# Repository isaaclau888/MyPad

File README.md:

# MyPad

MyPad is a tiny, pocket-sized macro pad I designed to clear up my desk and speed up my workflow. It has 9 mechanical keys, a vertical screen, and a dial knob, all packed into a super clean layout inspired by the classic look of the original 2001 Apple iPod. Instead of having a massive grid of keys, MyPad relies on clever software. By using multiple code layers and custom shortcuts, this little 3x3 pad can handle everything from jumping through complex lines of code in VS Code to tweaking 3D models in Fusion 360, all without my hand ever leaving the controller.

## What's it for?
MyPad is a tiny, physical shortcut box for your desk that saves you from stretching your fingers across awkward keyboard shortcuts. It condenses repetitive tasks—like copy-pasting, opening a terminal, or switching layers—into single tactile clicks. Plus, the built-in screen keeps track of your settings while the dial knob gives you smooth, hands-on control over your music volume or timeline scrolling.

## How to build it?
Please print all the 3D parts. <p>

# 3D Parts Assembly
Step 1: Solder the Base Electronics <br>
Solder all base components directly onto your PCB. This includes the Seeed Studio XIAO RP2040, the SSD1306 OLED Screen, the IN4148 Diodes, and the EC11 Rotary Encoder. Ensure they sit flat against the PCB surface before soldering. <p>

Step 2: Prepare the Top Plate <br>
Take your top case part (which acts as your top switch plate). Push all of your mechanical switches into the 14.0mm x 14.0mm square cutouts from the top side until they click tightly into place. <p>

Step 3: Combine and Solder the Switches <br>
Align the metal pins of the switches (now held in the top plate) with the empty switch holes on your PCB. Press the top plate assembly firmly down onto the PCB until the bottom of the switches rest flush against the PCB. Flip the assembly over and solder the switch pins from the back of the PCB. <p>

Step 4: Mount into the Bottom Case <br>
Place your fully soldered core assembly into the bottom case. Make sure the Seeed Studio XIAO's USB-C port aligns perfectly with the cutout pocket in the case wall, then secure the top and bottom halves together using your housing screws. <p>

Step 5: Final Touches <br>
Push your keycaps onto the switch stems. Your MyPad is complete! <p>

## How to Install Firmware?

1. Copy Folder to QMK
Clone this repository, then copy or move the **`MyPad Firmware`** folder into your local QMK directory:
`qmk_firmware/keyboards/`

2. Compile the Code
Open your terminal inside your `qmk_firmware` folder and run this command: qmk compile -kb "MyPad Firmware" -km default <p>
(Make sure to keep the quotation marks around the folder name in your terminal so it reads the space correctly!) This creates a file named `mypad_firmware_default.uf2`.

3. Flash the RP2040

4. Unplug the USB-C cable from your MyPad.
  
5. Hold down the physical **BOOTSEL** button on the tiny XIAO board while plugging the cable back into your computer.

6. A folder named **RPI-RP2** will pop up on your computer like a regular USB flash drive.

7. Drag and drop the `.uf2` file right into that folder. <p>

The drive will automatically close itself, and your MyPad is ready to go!

## Why did I make it?
I decided to make this because I want a custom keyboard that works like a Stream Deck.

## How I made it?
I used Fusion 360 to make the case, VS Code and Terminal for the coding part, KiCad for the PCB board and last but not least, the parts from the BOM.

# Schematic and PCB

# BOM

|   |                                           |    |           |                 |          |        |              |              |              |                                                                                                                                                                                                                                                                                                                                                                                                                                                                                                                                                                                                                              |                      |
|---|-------------------------------------------|----|-----------|-----------------|----------|--------|--------------|--------------|--------------|------------------------------------------------------------------------------------------------------------------------------------------------------------------------------------------------------------------------------------------------------------------------------------------------------------------------------------------------------------------------------------------------------------------------------------------------------------------------------------------------------------------------------------------------------------------------------------------------------------------------------|----------------------|
|   |Description                                |Item|Usage Count|Purchase Quantity|Unit Price|Subtotal|Price(HKD) [$]|Price(RMB) [$]|Price(USD) [$]|Link                                                                                                                                                                                                                                                                                                                                                                                                                                                                                                                                                                                                                          |Additional description|
|   |Electrical Components                      |    |           |                 |          |        |              |              |              |                                                                                                                                                                                                                                                                                                                                                                                                                                                                                                                                                                                                                              |                      |
|   |PCB Board                                  |    |1          |1                |$54.86    |$54.86  |$54.86        |$47.39        |$7.00         |https://jlcpcb.com/                                                                                                                                                                                                                                                                                                                                                                                                                                                                                                                                                                                                           |                      |
|   |Seeed Studio XIAO RP2040                   |    |1          |1                |$28.94    |$28.94  |$28.94        |$25.00        |$3.69         |https://item.taobao.com/item.htm?id=658626117798&spm=a312a.7700824.w4002-26059791966.9.60d933db6lhayb&skuId=5902864067685                                                                                                                                                                                                                                                                                                                                                                                                                                                                                                     |                      |
|   |Cherry MX Switches                         |    |9          |1                |$23.15    |$23.15  |$23.15        |$20.00        |$2.95         |https://item.taobao.com/item.htm?id=615897479067&mi_id=0000G49e9UiDHmvNbZuIxEqx0hhavdGOtj9aIAB91MIe1Xs&skuId=5076329578956&spm=a21xtw.29978518.0.0&xxc=shop                                                                                                                                                                                                                                                                                                                                                                                                                                                                   |                      |
|   |SSD1306 0.91 OLED 4pin 128x32              |    |1          |1                |$14.31    |$14.31  |$14.31        |$12.36        |$1.83         |https://detail.tmall.com/item.htm?abbucket=10&id=617450807815&pisk=haVnhu_M-U1gsNB9ovmTOubTxOCvjU4bu0dpUXrGUuUYpYRK9Y7uccd-p9ZRrRqzfvnEvwGoUurEUun8JXaINu_-M7NnbFu47BRr4GfKoQlPDiCozING2kpenp1eQVosrBJrLuua74nZ8pRz4ckZu4REabrz7N0ou4REavJZbq3oaLkeTVRZP2oyYQke_N0Sb0lraulNS4iZ4blPy6zhP04-iJ8sbs9JaQPhOv0fGcRyZ5D-KmRxjMB6dxMuxvVOtng3Qr0r-u1XOXkuL-lUZifn_rwTYVqPmLxE3LJkcPaLzK6NvZ48KxEwHtPGSrEQF8AerJj7BSa_ohIPiGN_xPaDY9j5dceYW5YADwwg7-FgcC7Vli4gYREBbtf8Z8NASmnW4YIpSA3NyNbM3-ME525ASNvWzvusSmQGSK5ZLVgFM&rn=3f79f2344ea3bbee7ca7e121c52b7942&skuId=5074992704097&spm=a312a.7700824.w4011-23941273512.47.1fdd6dcbe1g9gy|                      |
|   |Rotary Encoder EC11E Switch Vertical H20mm |    |1          |1                |$3.36     |$3.36   |$3.36         |$2.90         |$0.43         |https://detail.tmall.com/item.htm?abbucket=10&id=614080038092&pisk=hNdshEfvYFghm1fqL2bDZ8fgSs5vXnSV0EIA5MjTuAb4GpTJxZ5qmEQvGn-dgtnG_ItBk3gGucA2drTkA2oraZqgFbfu65FT0wId7m46wDhySFjczpXtdKPL3N73HSKABMeduMFTHiKA9MQlv5QY6sIKRZjdDsBADXhdoNFTXsCxRJQVyiEAMsILJZb1ksCvDe3CoMQOMsKvJ2_cyKRKqPLrkzj1SqPPCgLKKSenuNCPVFCzTWzc5EXbYsVtNMpwHC5p6D3O9UveXw1SGr_BFeCO5ncus1LJJKKFHSy9gsot5E8JyQeolXnBoe9kJ-ckGdKCaCYzSjDS2CYfthrZJYiJOB-CLfqqeBpDbExYKXRKeBLBUKemgCokLLR6sRh9n-czJyKHBFw2qOQh8muIR88cBwbC52gQn-XO-w5IR2wyo&rn=da8786ba5e99918c28a8c938c6b7e189&spm=a312a.7700824.w4011-23941273512.42.49ed6dcbJybH2l&skuId=4495430251556|                      |
|   |1u Keycaps                                 |    |9          |1                |$11.58    |$11.58  |$11.58        |$10.00        |$1.48         |https://item.taobao.com/item.htm?id=739962388435&spm=a312a.7700824.w4002-15015765193.11.7d6ea607QcT1D0&skuId=5107854577164                                                                                                                                                                                                                                                                                                                                                                                                                                                                                                    |                      |
|   |IN4148 switching diodes, through-hole DO-35|    |9          |1                |$5.33     |$5.33   |$5.33         |$4.60         |$0.68         |https://detail.tmall.com/item.htm?abbucket=10&id=41209807837&pisk=ha7Se2Td3yXyKUYU0SY1krYoZe8pJ9JeL6ppNKv-87XERpBRNHHyzHPBOK1947XFLi9CHt9RzuvERv6ATb-d8p7BreYdSGHN3Y4v9CzEJpd-qzUa2Rya7yixSKyCT0FfAtnvsKd-yBK8GmdeTedpweFXHBOMp4BpJS1vnBo-yLpJkKdBwbLpp3KAMQRJpY3pexFXtKdJw9LLGEpD9epdpeQ8GZeiw8nmTpdTTV-WBsEmJxNewFv1wC0jlDA5tHiXC4U6HgSdzEQ8H7LAsiWJGFaIOIs1MUd5KP0ky1CAvHSm80Qe8yyFqs5NKxaQXZfl1TjxZ5q7T1YRb6mzV74FzEQR0jr1R-JAaU-_o2qNrwWPn9Umpl_dy6SB0XiV2Rppu6CIgVSnxPlxMt4QECBp2IA4LSNjb6xJiIO7GSinx3dDgENbGc5h.&rn=cc2dcf6003a317450cddac3927fc9ef0&spm=a312a.7700824.w4011-25323366171.258.76c21ebbyisjSf            |                      |
|   |                                           |    |           |                 |Total     |        |$141.53       |$122.25       |$18.06        |                                                                                                                                                                                                                                                                                                                                                                                                                                                                                                                                                                                                                              |                      |

# Fallout Zine

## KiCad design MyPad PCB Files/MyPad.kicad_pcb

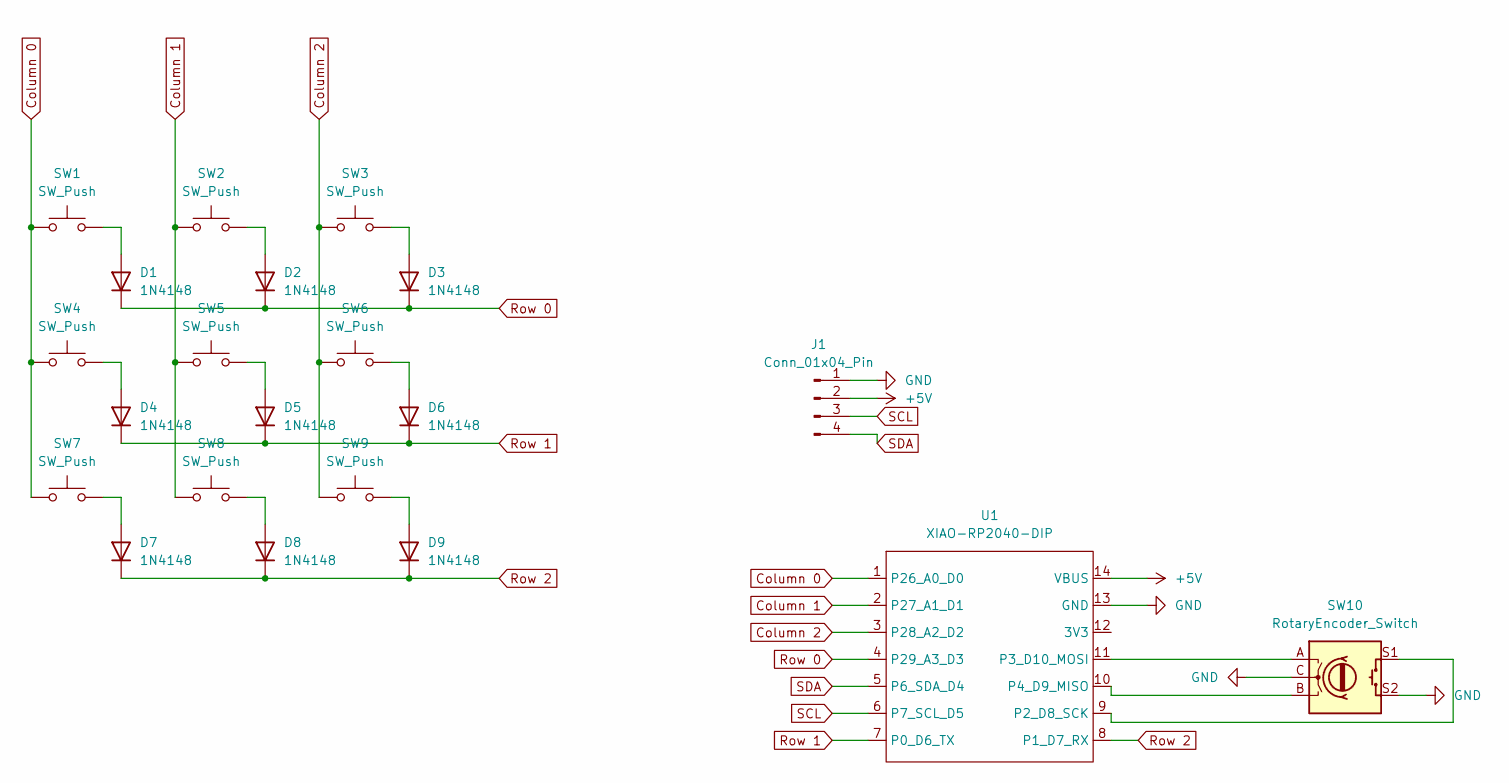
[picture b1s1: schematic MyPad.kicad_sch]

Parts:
D1, D2, D3, D4, D5, D6, D7, D8, D9: 1N4148; D_DO-35_SOD27_P7.62mm_Horizontal
J1: Conn_01x04_Pin; SSD1306-0.91-OLED-4pin-128x32
SW1, SW2, SW3, SW4, SW5, SW6, SW7, SW8, SW9: SW_Push; SW_Cherry_MX_1.00u_PCB
SW10: RotaryEncoder_Switch; RotaryEncoder_Alps_EC11E-Switch_Vertical_H20mm
U1: XIAO-RP2040-DIP

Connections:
+5V: J1.2, U1.14 (VBUS)
Column 0: SW1.1, SW4.1, SW7.1, U1.1 (P26_A0_D0)
Column 1: SW2.1, SW5.1, SW8.1, U1.2 (P27_A1_D1)
Column 2: SW3.1, SW6.1, SW9.1, U1.3 (P28_A2_D2)
GND: J1.1, SW10.C, SW10.S2, U1.13 (GND)
unnamed: D1.2 (A), SW1.2
unnamed: D2.2 (A), SW2.2
unnamed: D3.2 (A), SW3.2
unnamed: D4.2 (A), SW4.2
unnamed: D5.2 (A), SW5.2
unnamed: D6.2 (A), SW6.2
unnamed: D7.2 (A), SW7.2
unnamed: D8.2 (A), SW8.2
unnamed: D9.2 (A), SW9.2
unnamed: SW10.S1, U1.9 (P2_D8_SCK)
unnamed: SW10.A, U1.11 (P3_D10_MOSI)
unnamed: SW10.B, U1.10 (P4_D9_MISO)
Row 0: D1.1 (K), D2.1 (K), D3.1 (K), U1.4 (P29_A3_D3)
Row 1: D4.1 (K), D5.1 (K), D6.1 (K), U1.7 (P0_D6_TX)
Row 2: D7.1 (K), D8.1 (K), D9.1 (K), U1.8 (P1_D7_RX)
SCL: J1.3, U1.6 (P7_SCL_D5)
SDA: J1.4, U1.5 (P6_SDA_D4)

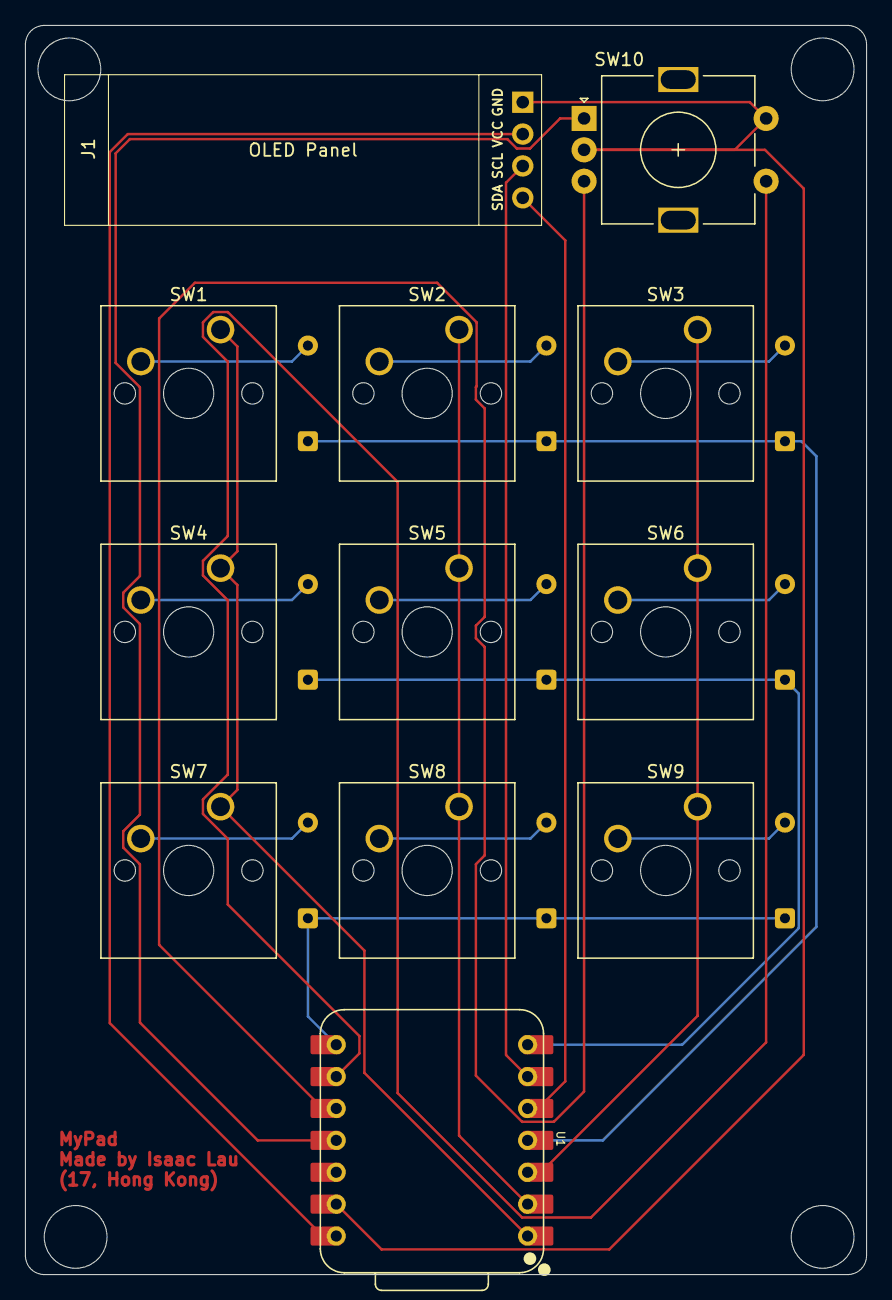
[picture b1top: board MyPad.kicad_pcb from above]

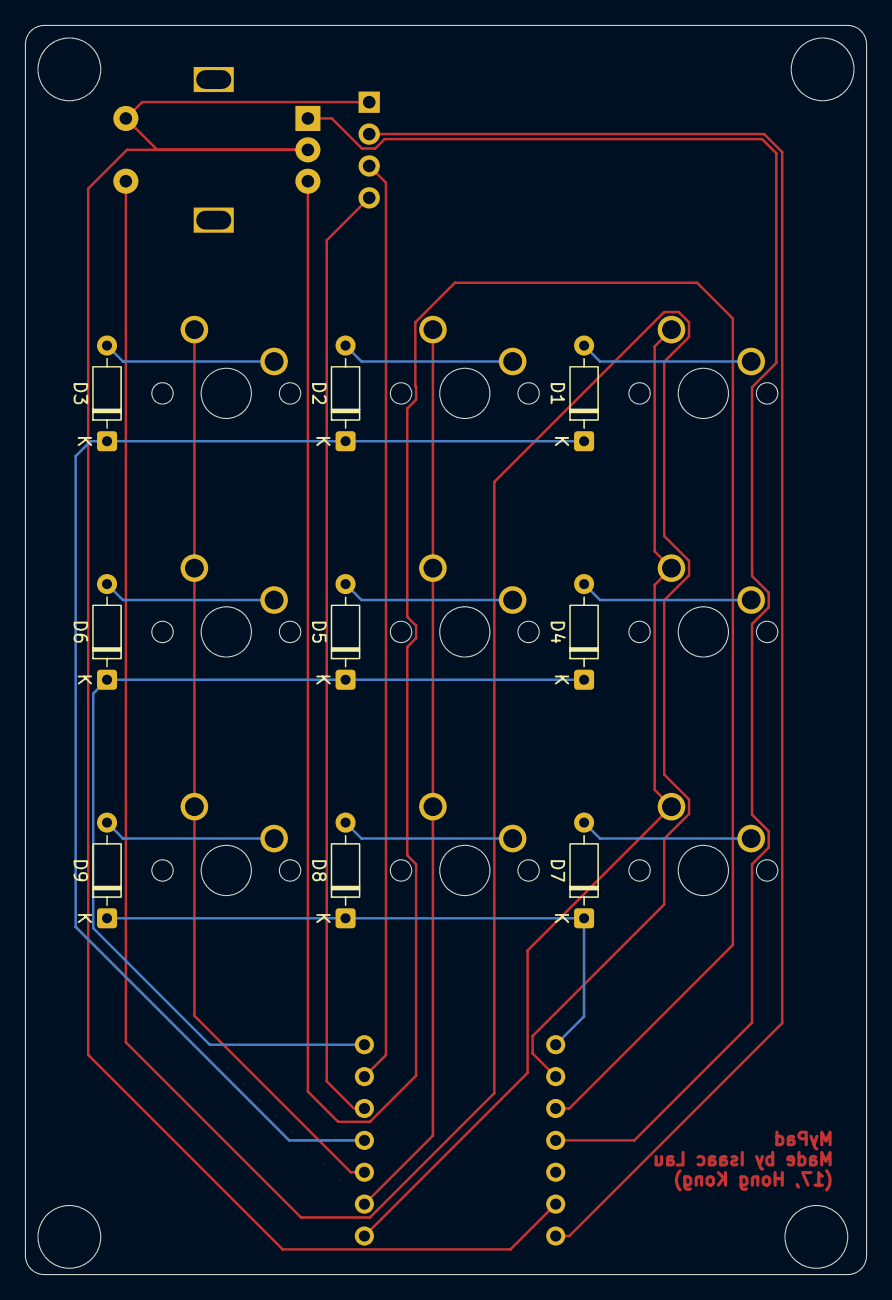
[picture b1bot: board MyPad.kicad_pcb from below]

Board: 2 copper layers, 67.0 x 99.5 mm, 21 parts (9 on the bottom side), 22 nets.

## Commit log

2026-06-26 Modify assembly instructions and update image
    Updated an image link in the assembly instructions and added a step for placing the top part.
